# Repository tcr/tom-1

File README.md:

# TOM-1

https://hackaday.io/project/171965-ttl-operation-module-tom-1

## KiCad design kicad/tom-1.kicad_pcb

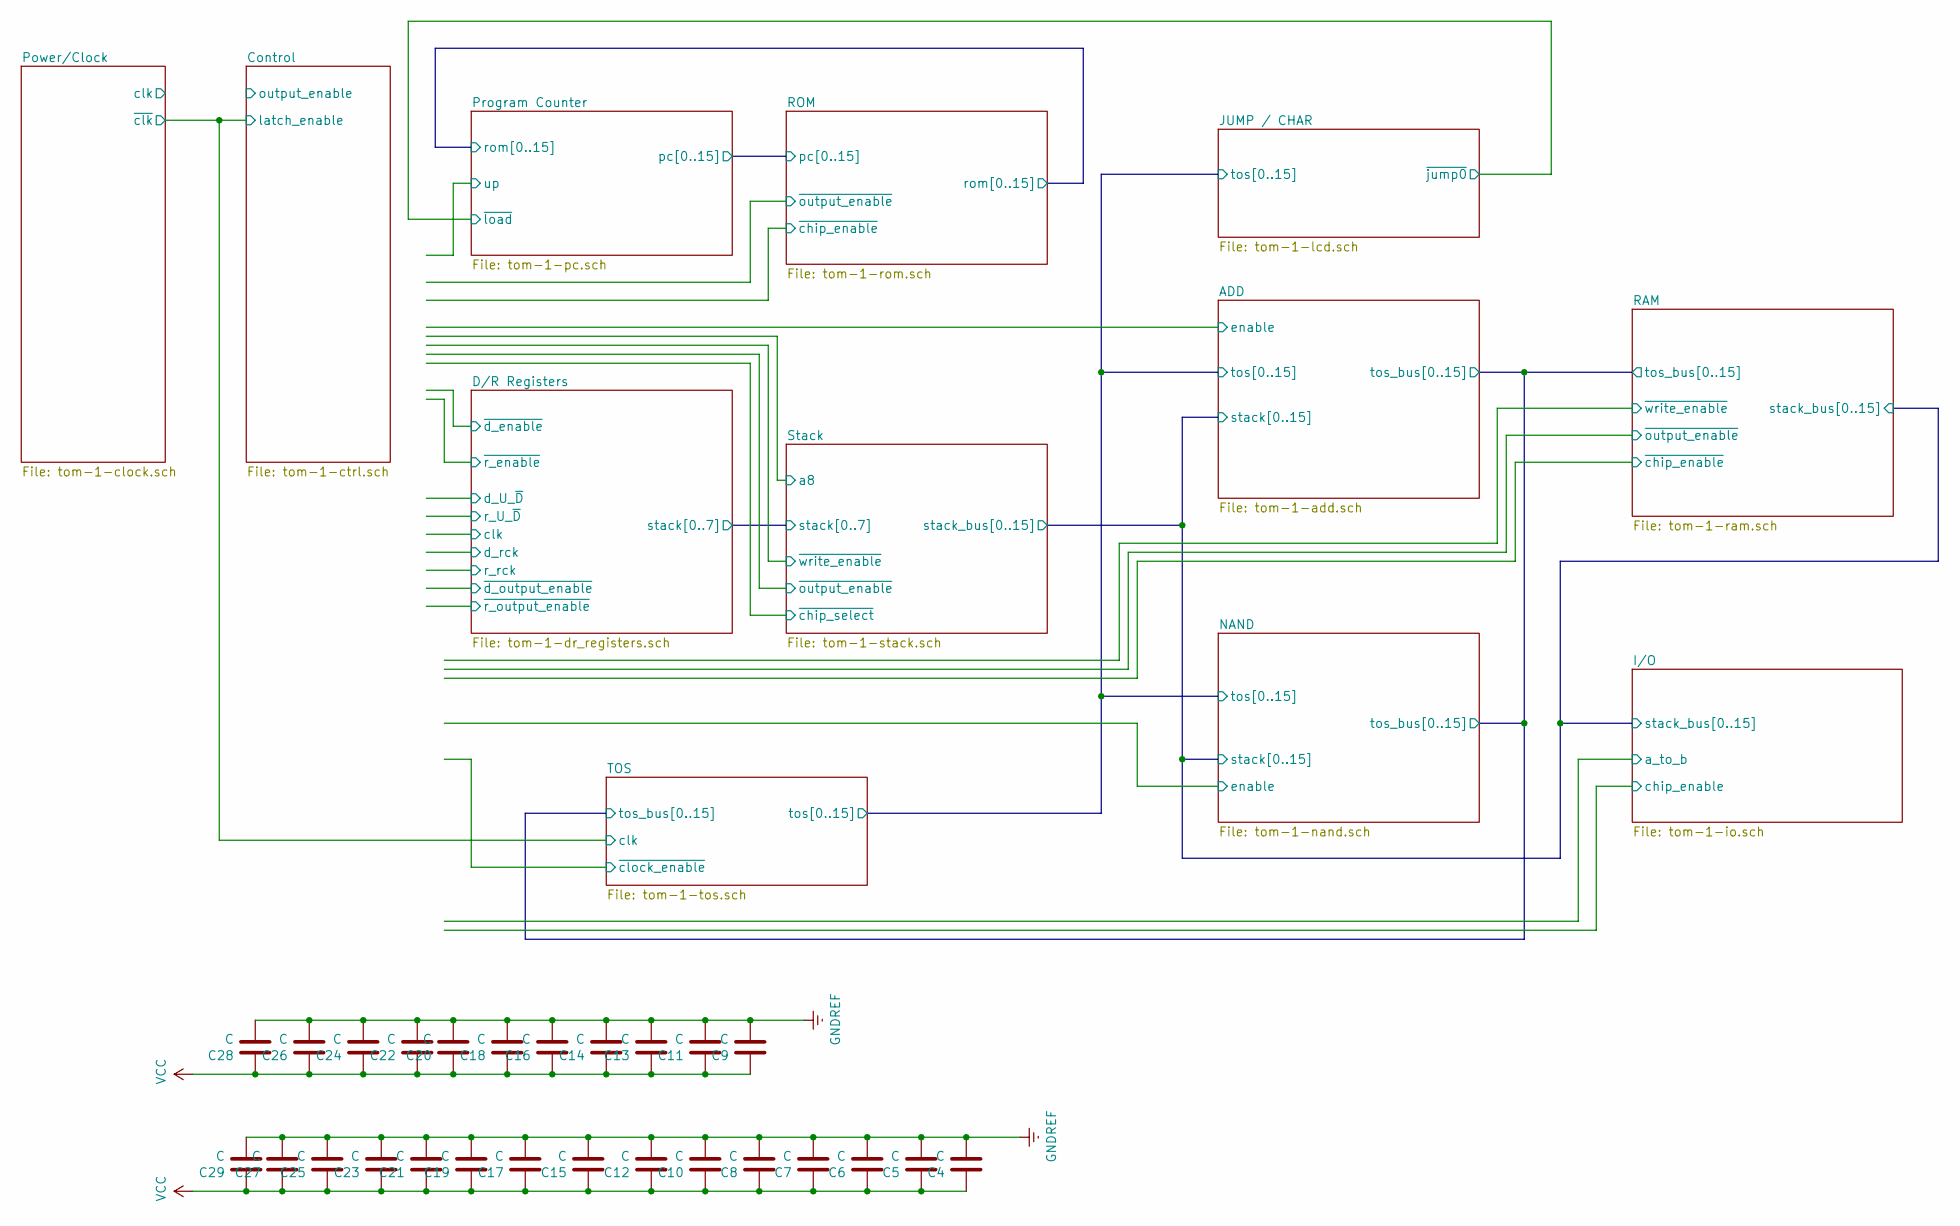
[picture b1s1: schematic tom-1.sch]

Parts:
C4, C5, C6, C7, C8, C9, C10, C11, C12, C13, C14, C15, C16, C17, C18, C19, C20, C21, C22, C23, C24, C25, C26, C27, C28, C29: C; C_Disc_D3.0mm_W1.6mm_P2.50mm

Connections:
GNDREF: C4.2, C5.1, C6.1, C7.1, C8.1, C9.2, C10.2, C11.2, C12.2, C13.2, C14.2, C15.2, C16.2, C17.2, C18.2, C19.2, C20.2, C21.2, C22.2, C23.2, C24.2, C25.2, C26.2, C27.2, C28.2, C29.2; also elsewhere on the board
VCC: C4.1, C5.2, C6.2, C7.2, C8.2, C9.1, C10.1, C11.1, C12.1, C13.1, C14.1, C15.1, C16.1, C17.1, C18.1, C19.1, C20.1, C21.1, C22.1, C23.1, C24.1, C25.1, C26.1, C27.1, C28.1, C29.1; also elsewhere on the board

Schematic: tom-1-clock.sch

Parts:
C1, C2, C3: C; C_Disc_D4.7mm_W2.5mm_P5.00mm
C30: 10uF; C_Disc_D3.0mm_W1.6mm_P2.50mm
D1: DIODE; D_DO-41_SOD81_P2.54mm_Vertical_AnodeUp
D2: LED; LED_D3.0mm
J2: USB Module; PinHeader_1x06_P2.54mm_Vertical
JP1: Jumper_NC_Dual; PinHeader_1x03_P2.54mm_Vertical
Q1: BC517; TO-92_Inline
R2, R3, R4, R7, R8, R9: R; R_Axial_DIN0204_L3.6mm_D1.6mm_P1.90mm_Vertical
R5: 1K; R_Axial_DIN0204_L3.6mm_D1.6mm_P1.90mm_Vertical
R6: 20K; R_Axial_DIN0204_L3.6mm_D1.6mm_P1.90mm_Vertical
SW1, SW2: SW_PUSH; SW_PUSH_6mm
U8: LM555xN; DIP-8_W7.62mm

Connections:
/Power/Clock/clk: R7.2, U8.3 (Q)
/TOS/clk: Q1.1 (C), R8.2; also elsewhere on the board
GND: C2.2, C3.2, SW2.1, U8.1 (GND); also elsewhere on the board
GNDREF: C30.2, J2.2, Q1.3 (E), R9.2, SW1.1; also elsewhere on the board
unnamed: C1.1, D1.1 (K), JP1.1, R3.2
unnamed: C1.2, R2.2, SW2.2
unnamed: C2.1, R4.2, U8.6 (THR), U8.7 (DIS)
unnamed: D2.1, R9.1
unnamed: JP1.2, U8.2 (TR)
unnamed: Q1.2 (B), R7.1
unnamed: R5.2, SW1.2
VCC: C3.1, D1.2 (A), D2.2, J2.1, R2.1, R3.1, R4.1, R6.1, R8.1, U8.4 (R), U8.8 (VCC); also elsewhere on the board
~Reset: C30.1, R5.1, R6.2

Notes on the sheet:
Reset generation

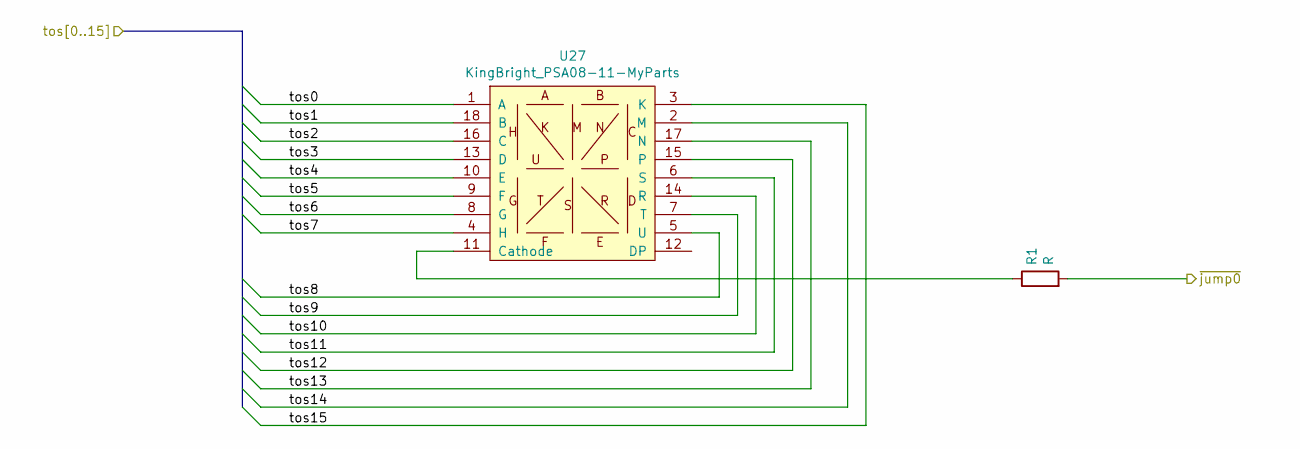
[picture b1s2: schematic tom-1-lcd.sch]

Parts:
R1: R; R_Axial_DIN0204_L3.6mm_D1.6mm_P1.90mm_Vertical
U27: KingBright_PSA08-11-MyParts; EightSegment

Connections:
/ADD/tos0: U27.1 (A); also elsewhere on the board
/ADD/tos1: U27.18 (B); also elsewhere on the board
/ADD/tos2: U27.16 (C); also elsewhere on the board
/ADD/tos3: U27.13 (D); also elsewhere on the board
/ADD/tos4: U27.10 (E); also elsewhere on the board
/ADD/tos5: U27.9 (F); also elsewhere on the board
/ADD/tos6: U27.8 (G); also elsewhere on the board
/ADD/tos7: U27.4 (H); also elsewhere on the board
/ADD/tos8: U27.5 (U); also elsewhere on the board
/ADD/tos9: U27.7 (T); also elsewhere on the board
/ADD/tos10: U27.14 (R); also elsewhere on the board
/ADD/tos11: U27.6 (S); also elsewhere on the board
/ADD/tos12: U27.15; also elsewhere on the board
/ADD/tos13: U27.17 (N); also elsewhere on the board
/ADD/tos14: U27.2 (M); also elsewhere on the board
/ADD/tos15: U27.3 (K); also elsewhere on the board
/JUMP / CHAR/jump0: R1.2; also elsewhere on the board
unnamed: R1.1, U27.11 (Cathode)

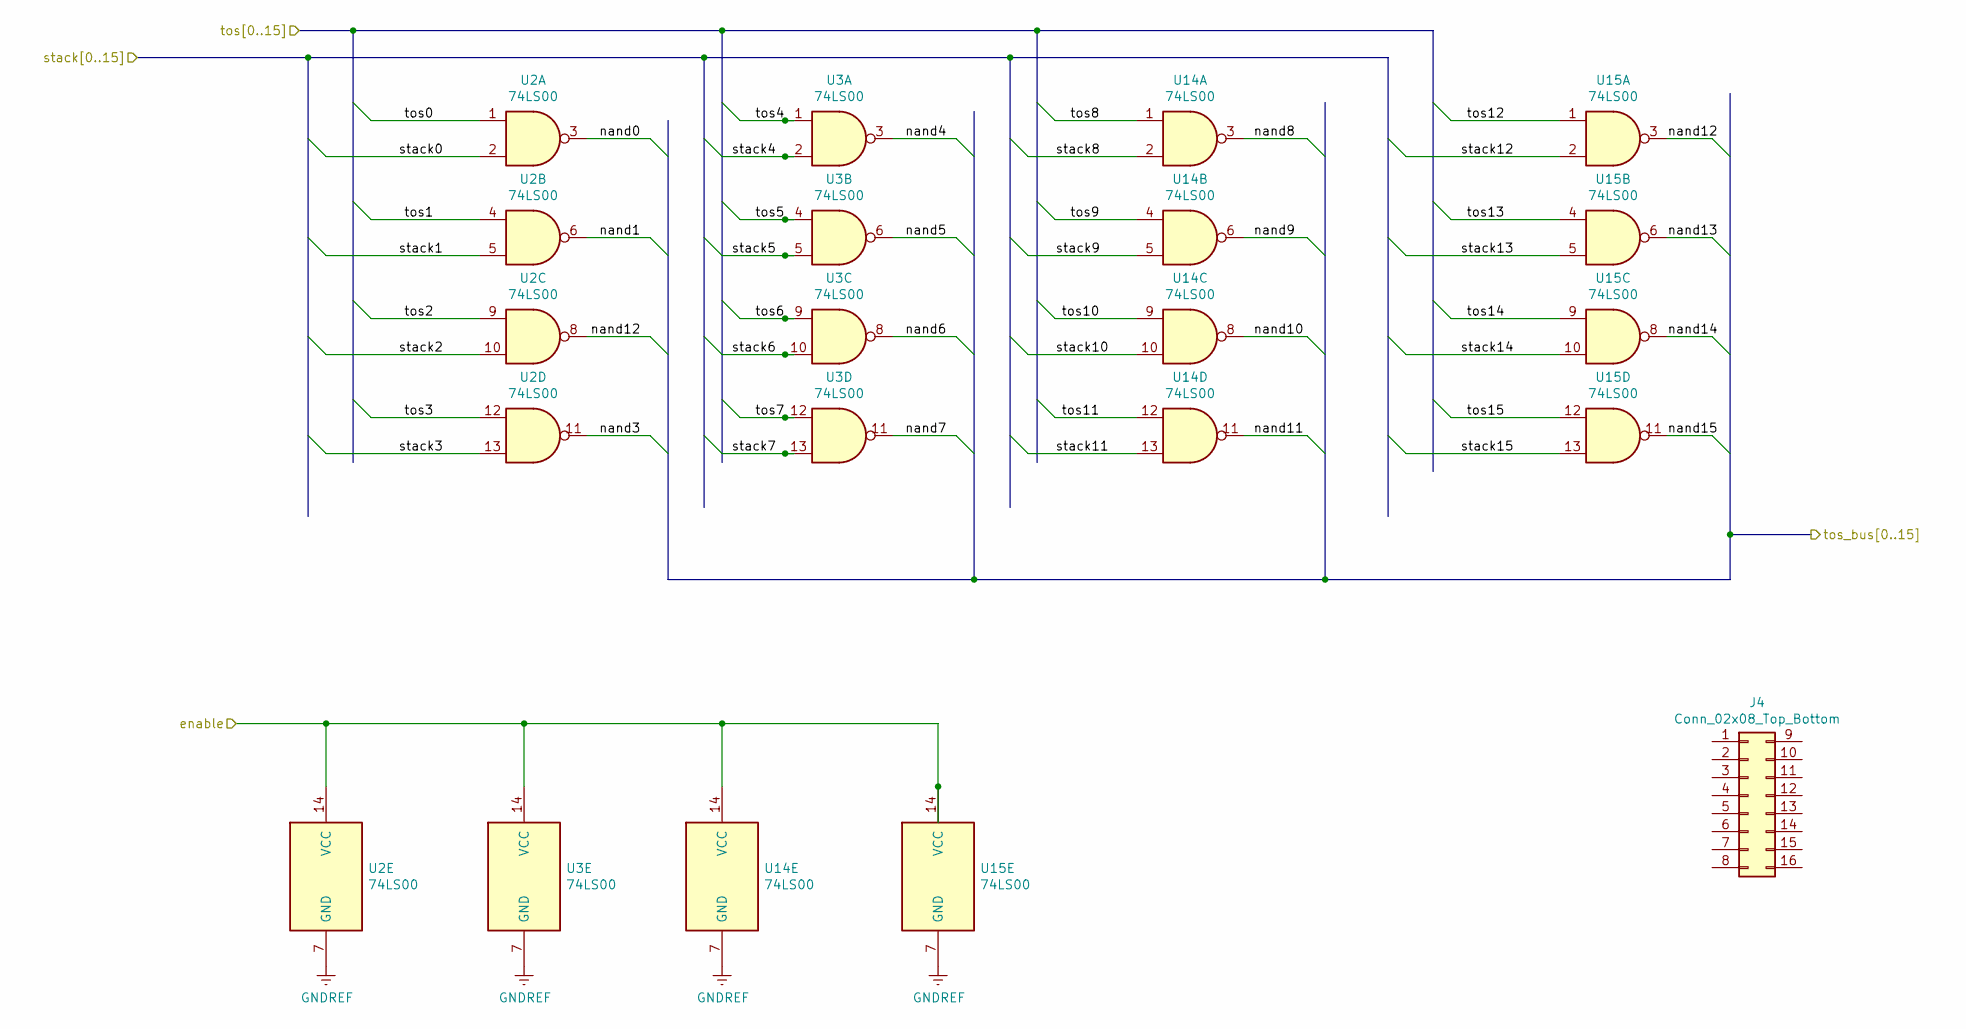
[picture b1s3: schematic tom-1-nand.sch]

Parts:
J4: Conn_02x08_Top_Bottom; PinSocket_2x09_P2.54mm_Vertical
U2, U3, U14, U15: 74LS00; DIP-14_W7.62mm

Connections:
/ADD/stack0: U2.2; also elsewhere on the board
/ADD/stack1: U2.5; also elsewhere on the board
/ADD/stack2: U2.10; also elsewhere on the board
/ADD/stack3: U2.13; also elsewhere on the board
/ADD/stack4: U3.2; also elsewhere on the board
/ADD/stack5: U3.5; also elsewhere on the board
/ADD/stack6: U3.10; also elsewhere on the board
/ADD/stack7: U3.13; also elsewhere on the board
/ADD/stack8: U14.2; also elsewhere on the board
/ADD/stack9: U14.5; also elsewhere on the board
/ADD/stack10: U14.10; also elsewhere on the board
/ADD/stack11: U14.13; also elsewhere on the board
/ADD/stack12: U15.2; also elsewhere on the board
/ADD/stack13: U15.5; also elsewhere on the board
/ADD/stack14: U15.10; also elsewhere on the board
/ADD/stack15: U15.13; also elsewhere on the board
/ADD/tos0: U2.1; also elsewhere on the board
/ADD/tos1: U2.4; also elsewhere on the board
/ADD/tos2: U2.9; also elsewhere on the board
/ADD/tos3: U2.12; also elsewhere on the board
/ADD/tos4: U3.1; also elsewhere on the board
/ADD/tos5: U3.4; also elsewhere on the board
/ADD/tos6: U3.9; also elsewhere on the board
/ADD/tos7: U3.12; also elsewhere on the board
/ADD/tos8: U14.1; also elsewhere on the board
/ADD/tos9: U14.4; also elsewhere on the board
/ADD/tos10: U14.9; also elsewhere on the board
/ADD/tos11: U14.12; also elsewhere on the board
/ADD/tos12: U15.1; also elsewhere on the board
/ADD/tos13: U15.4; also elsewhere on the board
/ADD/tos14: U15.9; also elsewhere on the board
/ADD/tos15: U15.12; also elsewhere on the board
/NAND/enable: U2.14 (VCC), U3.14 (VCC), U14.14 (VCC), U15.14 (VCC)
/NAND/nand0: U2.3
/NAND/nand1: U2.6
/NAND/nand3: U2.11
/NAND/nand4: U3.3
/NAND/nand5: U3.6
/NAND/nand6: U3.8
/NAND/nand7: U3.11
/NAND/nand8: U14.3
/NAND/nand9: U14.6
/NAND/nand10: U14.8
/NAND/nand11: U14.11
/NAND/nand12: U2.8, U15.3
/NAND/nand13: U15.6
/NAND/nand14: U15.8
/NAND/nand15: U15.11
GNDREF: U2.7 (GND), U3.7 (GND), U14.7 (GND), U15.7 (GND); also elsewhere on the board

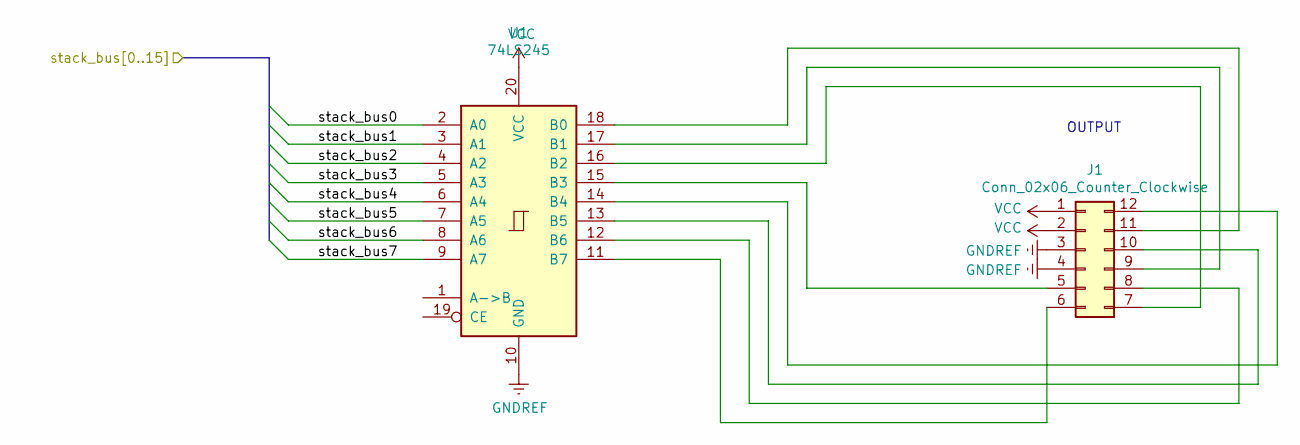
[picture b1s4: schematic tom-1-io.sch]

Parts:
J1: Conn_02x06_Counter_Clockwise; PinSocket_2x06_P2.54mm_Vertical
U1: 74LS245; DIP-20_W7.62mm

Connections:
/ADD/stack0: U1.2 (A0); also elsewhere on the board
/ADD/stack1: U1.3 (A1); also elsewhere on the board
/ADD/stack2: U1.4 (A2); also elsewhere on the board
/ADD/stack3: U1.5 (A3); also elsewhere on the board
/ADD/stack4: U1.6 (A4); also elsewhere on the board
/ADD/stack5: U1.7 (A5); also elsewhere on the board
/ADD/stack6: U1.8 (A6); also elsewhere on the board
/ADD/stack7: U1.9 (A7); also elsewhere on the board
GNDREF: J1.3, J1.4, U1.10 (GND); also elsewhere on the board
unnamed: J1.5, U1.15 (B3)
unnamed: J1.6, U1.11 (B7)
unnamed: J1.7, U1.16 (B2)
unnamed: J1.8, U1.12 (B6)
unnamed: J1.9, U1.17 (B1)
unnamed: J1.10, U1.13 (B5)
unnamed: J1.11, U1.18 (B0)
unnamed: J1.12, U1.14 (B4)
VCC: J1.1, J1.2, U1.20 (VCC); also elsewhere on the board

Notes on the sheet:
OUTPUT

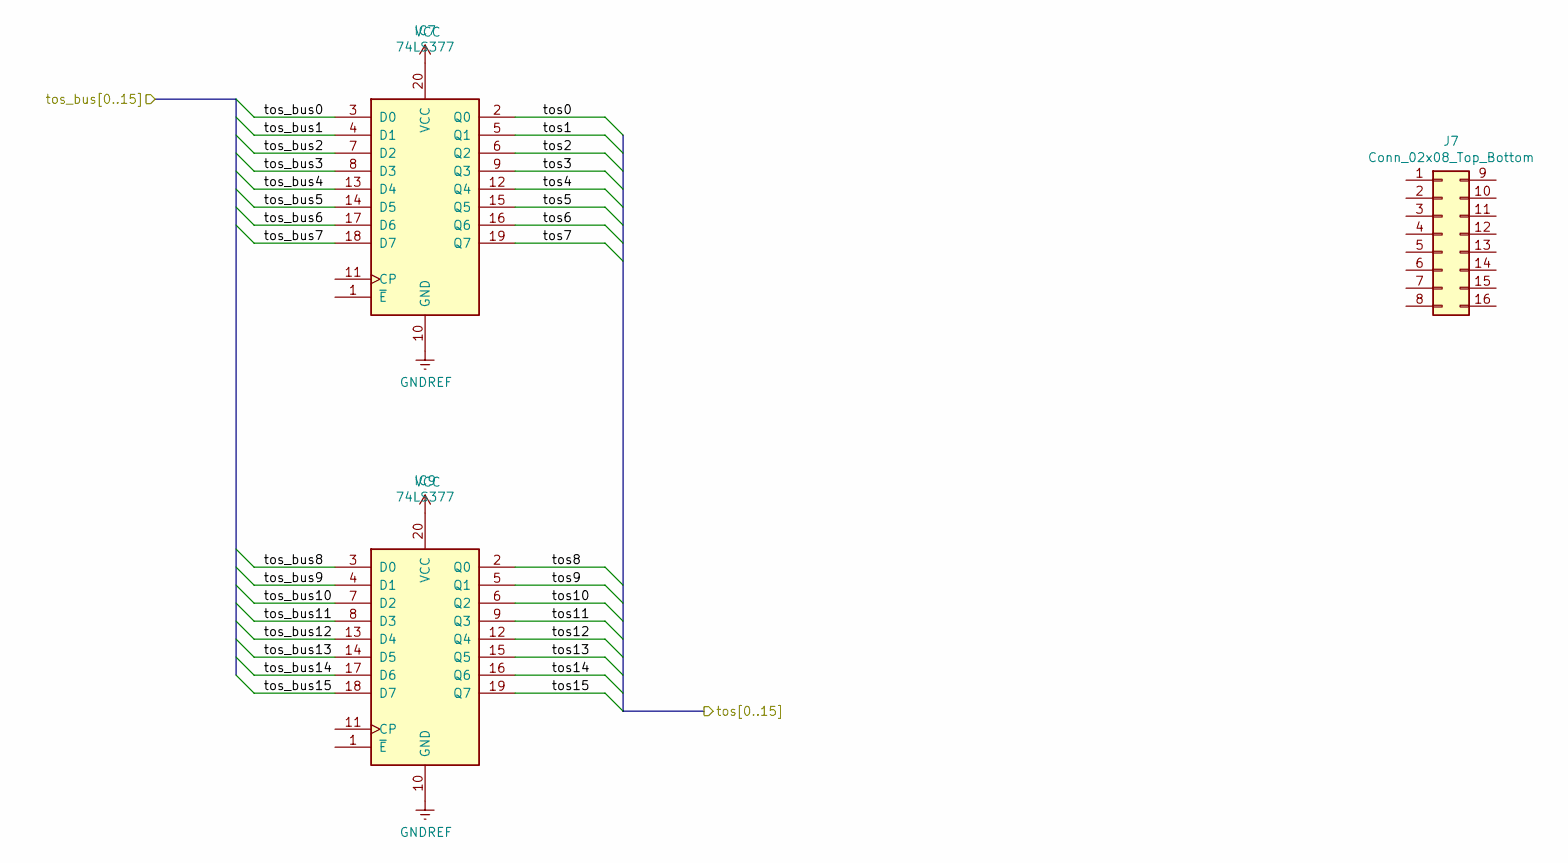
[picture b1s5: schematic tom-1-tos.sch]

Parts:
IC7, IC9: 74LS377; DIP-20_W7.62mm
J7: Conn_02x08_Top_Bottom; PinSocket_2x09_P2.54mm_Vertical

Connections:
/ADD/tos0: IC7.2 (Q0); also elsewhere on the board
/ADD/tos1: IC7.5 (Q1); also elsewhere on the board
/ADD/tos2: IC7.6 (Q2); also elsewhere on the board
/ADD/tos3: IC7.9 (Q3); also elsewhere on the board
/ADD/tos4: IC7.12 (Q4); also elsewhere on the board
/ADD/tos5: IC7.15 (Q5); also elsewhere on the board
/ADD/tos6: IC7.16 (Q6); also elsewhere on the board
/ADD/tos7: IC7.19 (Q7); also elsewhere on the board
/ADD/tos8: IC9.2 (Q0); also elsewhere on the board
/ADD/tos9: IC9.5 (Q1); also elsewhere on the board
/ADD/tos10: IC9.6 (Q2); also elsewhere on the board
/ADD/tos11: IC9.9 (Q3); also elsewhere on the board
/ADD/tos12: IC9.12 (Q4); also elsewhere on the board
/ADD/tos13: IC9.15 (Q5); also elsewhere on the board
/ADD/tos14: IC9.16 (Q6); also elsewhere on the board
/ADD/tos15: IC9.19 (Q7); also elsewhere on the board
/ADD/tos_bus0: IC7.3 (D0); also elsewhere on the board
/ADD/tos_bus1: IC7.4 (D1); also elsewhere on the board
/ADD/tos_bus2: IC7.7 (D2); also elsewhere on the board
/ADD/tos_bus3: IC7.8 (D3); also elsewhere on the board
/ADD/tos_bus4: IC7.13 (D4); also elsewhere on the board
/ADD/tos_bus5: IC7.14 (D5); also elsewhere on the board
/ADD/tos_bus6: IC7.17 (D6); also elsewhere on the board
/ADD/tos_bus7: IC7.18 (D7); also elsewhere on the board
/ADD/tos_bus8: IC9.3 (D0); also elsewhere on the board
/ADD/tos_bus9: IC9.4 (D1); also elsewhere on the board
/ADD/tos_bus10: IC9.7 (D2); also elsewhere on the board
/ADD/tos_bus11: IC9.8 (D3); also elsewhere on the board
/ADD/tos_bus12: IC9.13 (D4); also elsewhere on the board
/ADD/tos_bus13: IC9.14 (D5); also elsewhere on the board
/ADD/tos_bus14: IC9.17 (D6); also elsewhere on the board
/ADD/tos_bus15: IC9.18 (D7); also elsewhere on the board
/TOS/clk: IC7.11 (CP), IC9.11 (CP); also elsewhere on the board
/TOS/~clock_enable: IC7.1 (~E), IC9.1 (~E)
GNDREF: IC7.10 (GND), IC9.10 (GND); also elsewhere on the board
VCC: IC7.20 (VCC), IC9.20 (VCC); also elsewhere on the board

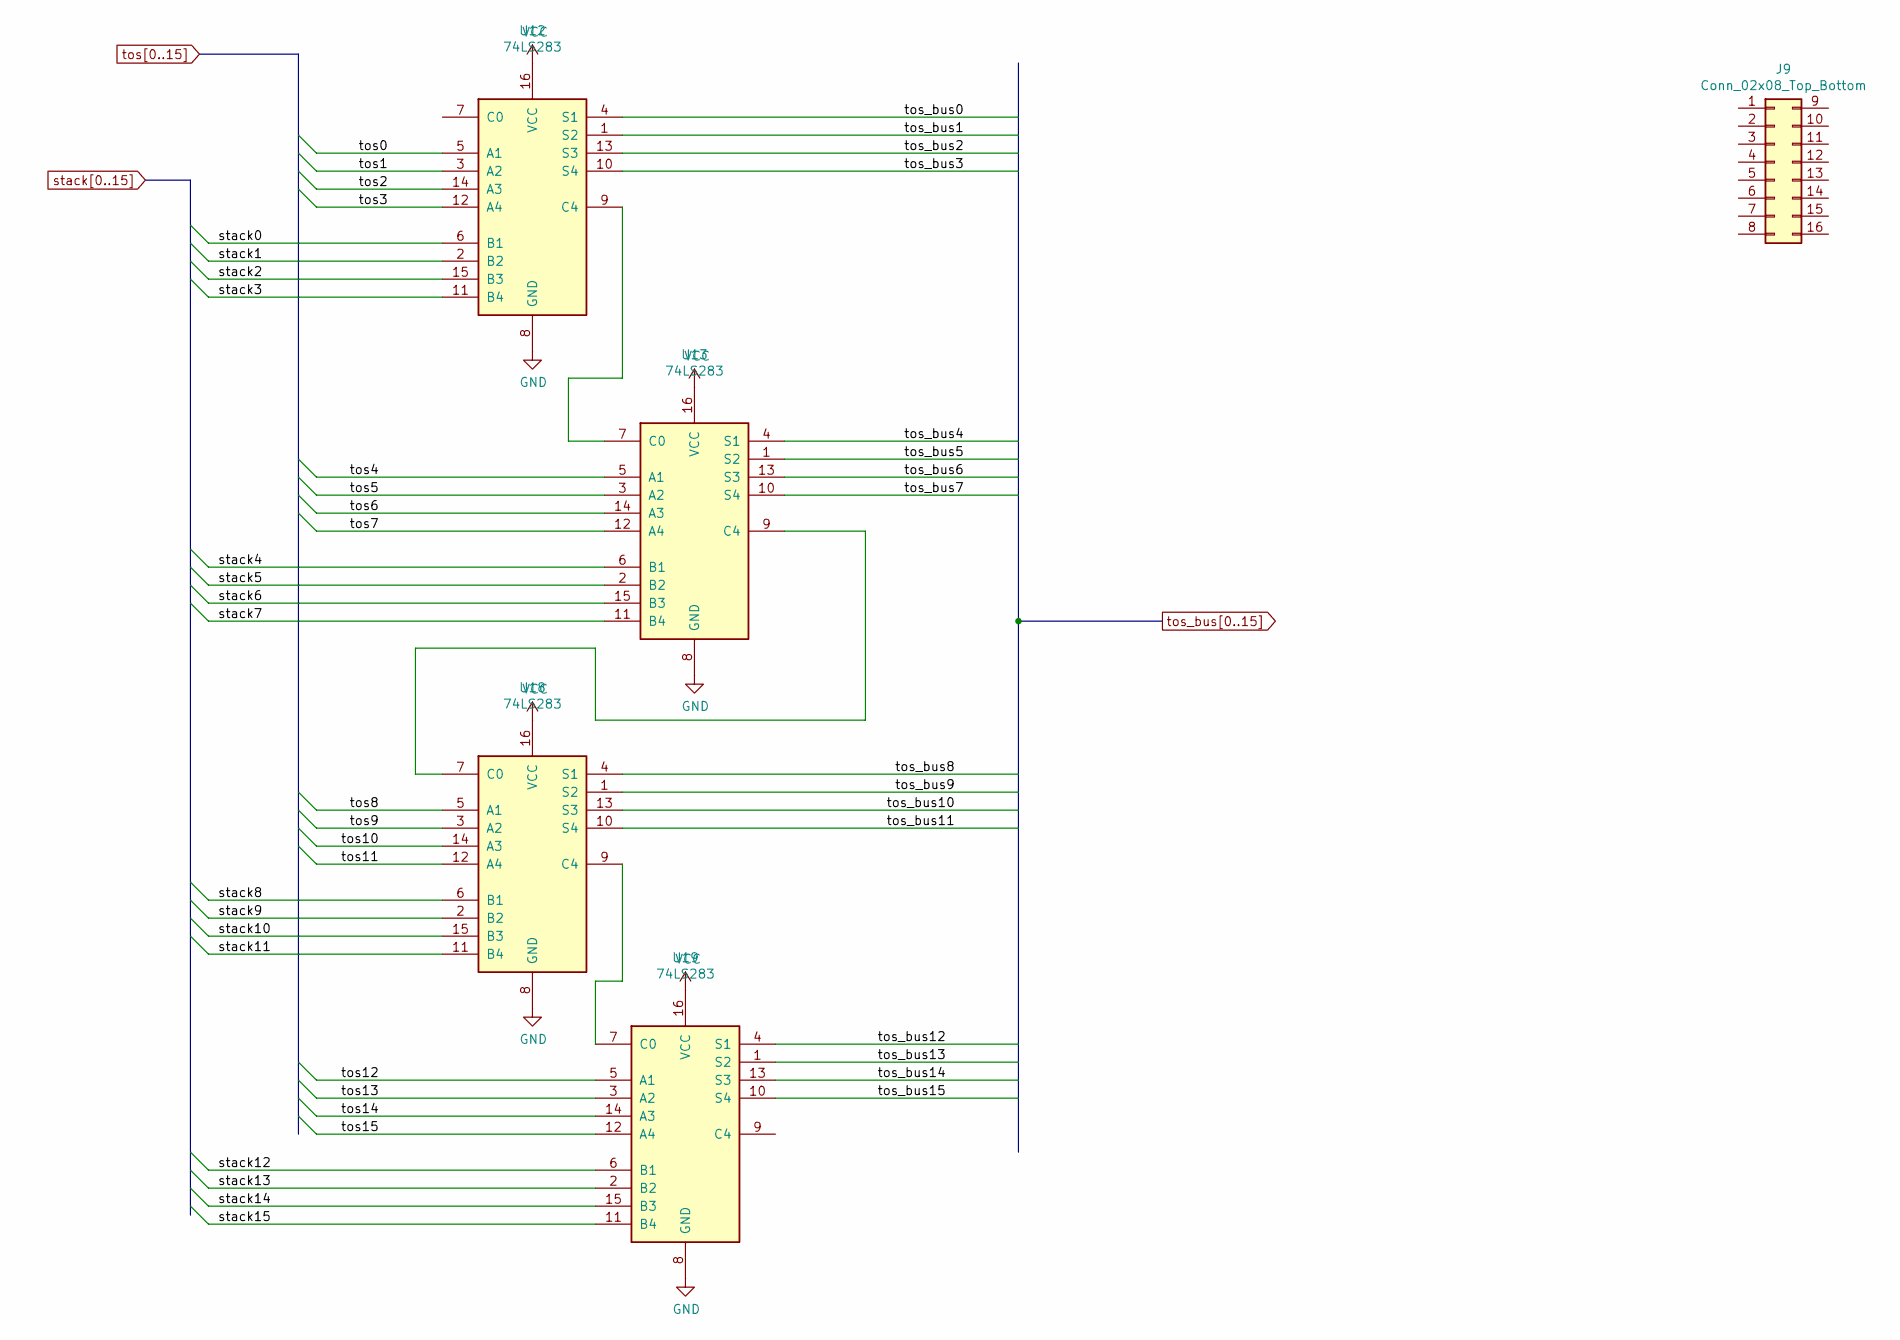
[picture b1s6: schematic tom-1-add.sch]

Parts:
J9: Conn_02x08_Top_Bottom; PinSocket_2x09_P2.54mm_Vertical
U12, U13, U18, U19: 74LS283; DIP-16_W7.62mm

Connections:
/ADD/enable: U12.16 (VCC), U13.16 (VCC), U18.16 (VCC), U19.16 (VCC)
/ADD/stack0: U12.6 (B1); also elsewhere on the board
/ADD/stack1: U12.2 (B2); also elsewhere on the board
/ADD/stack2: U12.15 (B3); also elsewhere on the board
/ADD/stack3: U12.11 (B4); also elsewhere on the board
/ADD/stack4: U13.6 (B1); also elsewhere on the board
/ADD/stack5: U13.2 (B2); also elsewhere on the board
/ADD/stack6: U13.15 (B3); also elsewhere on the board
/ADD/stack7: U13.11 (B4); also elsewhere on the board
/ADD/stack8: U18.6 (B1); also elsewhere on the board
/ADD/stack9: U18.2 (B2); also elsewhere on the board
/ADD/stack10: U18.15 (B3); also elsewhere on the board
/ADD/stack11: U18.11 (B4); also elsewhere on the board
/ADD/stack12: U19.6 (B1); also elsewhere on the board
/ADD/stack13: U19.2 (B2); also elsewhere on the board
/ADD/stack14: U19.15 (B3); also elsewhere on the board
/ADD/stack15: U19.11 (B4); also elsewhere on the board
/ADD/tos0: U12.5 (A1); also elsewhere on the board
/ADD/tos1: U12.3 (A2); also elsewhere on the board
/ADD/tos2: U12.14 (A3); also elsewhere on the board
/ADD/tos3: U12.12 (A4); also elsewhere on the board
/ADD/tos4: U13.5 (A1); also elsewhere on the board
/ADD/tos5: U13.3 (A2); also elsewhere on the board
/ADD/tos6: U13.14 (A3); also elsewhere on the board
/ADD/tos7: U13.12 (A4); also elsewhere on the board
/ADD/tos8: U18.5 (A1); also elsewhere on the board
/ADD/tos9: U18.3 (A2); also elsewhere on the board
/ADD/tos10: U18.14 (A3); also elsewhere on the board
/ADD/tos11: U18.12 (A4); also elsewhere on the board
/ADD/tos12: U19.5 (A1); also elsewhere on the board
/ADD/tos13: U19.3 (A2); also elsewhere on the board
/ADD/tos14: U19.14 (A3); also elsewhere on the board
/ADD/tos15: U19.12 (A4); also elsewhere on the board
/ADD/tos_bus0: U12.4 (S1); also elsewhere on the board
/ADD/tos_bus1: U12.1 (S2); also elsewhere on the board
/ADD/tos_bus2: U12.13 (S3); also elsewhere on the board
/ADD/tos_bus3: U12.10 (S4); also elsewhere on the board
/ADD/tos_bus4: U13.4 (S1); also elsewhere on the board
/ADD/tos_bus5: U13.1 (S2); also elsewhere on the board
/ADD/tos_bus6: U13.13 (S3); also elsewhere on the board
/ADD/tos_bus7: U13.10 (S4); also elsewhere on the board
/ADD/tos_bus8: U18.4 (S1); also elsewhere on the board
/ADD/tos_bus9: U18.1 (S2); also elsewhere on the board
/ADD/tos_bus10: U18.13 (S3); also elsewhere on the board
/ADD/tos_bus11: U18.10 (S4); also elsewhere on the board
/ADD/tos_bus12: U19.4 (S1); also elsewhere on the board
/ADD/tos_bus13: U19.1 (S2); also elsewhere on the board
/ADD/tos_bus14: U19.13 (S3); also elsewhere on the board
/ADD/tos_bus15: U19.10 (S4); also elsewhere on the board
GND: U12.8 (GND), U13.8 (GND), U18.8 (GND), U19.8 (GND); also elsewhere on the board
GNDREF: U12.7 (C0); also elsewhere on the board
unnamed: U12.9 (C4), U13.7 (C0)
unnamed: U13.9 (C4), U18.7 (C0)
unnamed: U18.9 (C4), U19.7 (C0)

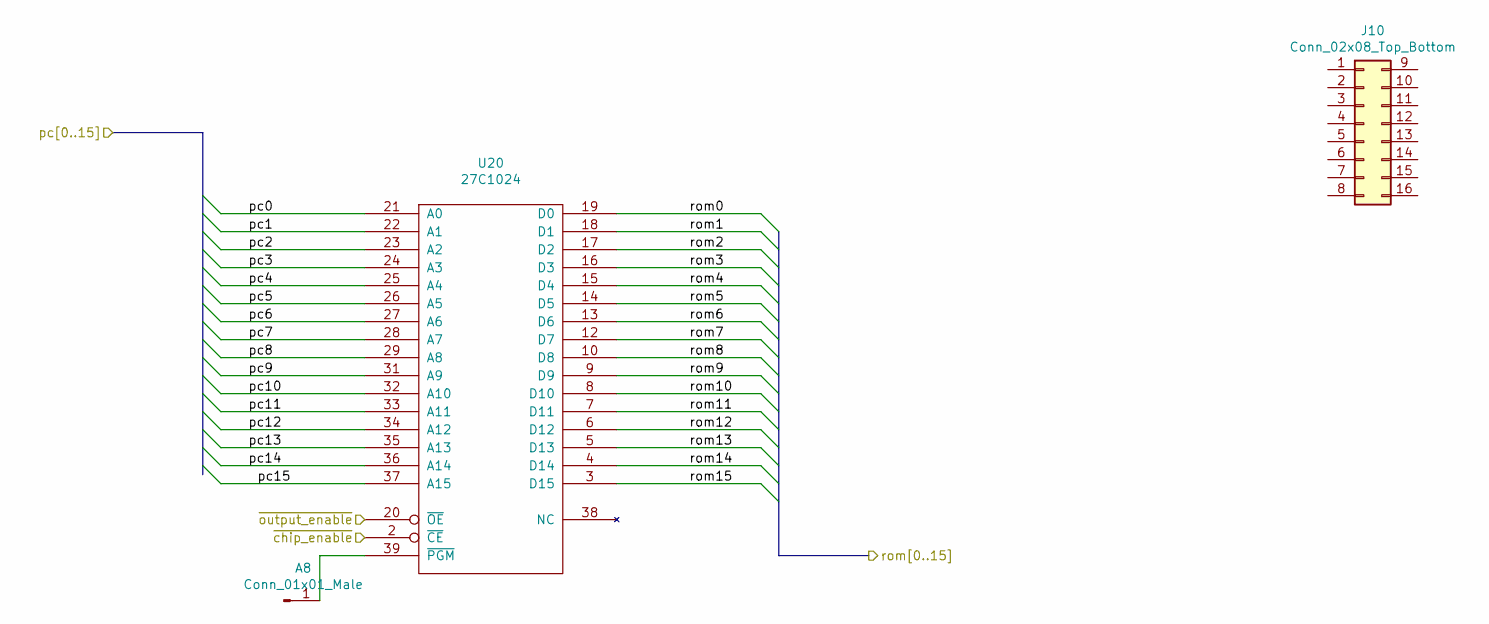
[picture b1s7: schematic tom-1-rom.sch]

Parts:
A8: Conn_01x01_Male; PinHeader_1x01_P2.54mm_Vertical
J10: Conn_02x08_Top_Bottom; PinSocket_2x09_P2.54mm_Vertical
U20: 27C1024; DIP-40_W15.24mm_Socket

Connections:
/Program Counter/pc0: U20.21 (A0); also elsewhere on the board
/Program Counter/pc1: U20.22 (A1); also elsewhere on the board
/Program Counter/pc2: U20.23 (A2); also elsewhere on the board
/Program Counter/pc3: U20.24 (A3); also elsewhere on the board
/Program Counter/pc4: U20.25 (A4); also elsewhere on the board
/Program Counter/pc5: U20.26 (A5); also elsewhere on the board
/Program Counter/pc6: U20.27 (A6); also elsewhere on the board
/Program Counter/pc7: U20.28 (A7); also elsewhere on the board
/Program Counter/pc8: U20.29 (A8); also elsewhere on the board
/Program Counter/pc9: U20.31 (A9); also elsewhere on the board
/Program Counter/pc10: U20.32 (A10); also elsewhere on the board
/Program Counter/pc11: U20.33 (A11); also elsewhere on the board
/Program Counter/pc12: U20.34 (A12); also elsewhere on the board
/Program Counter/pc13: U20.35 (A13); also elsewhere on the board
/Program Counter/pc14: U20.36 (A14); also elsewhere on the board
/Program Counter/pc15: U20.37 (A15); also elsewhere on the board
/Program Counter/rom0: U20.19 (D0); also elsewhere on the board
/Program Counter/rom1: U20.18 (D1); also elsewhere on the board
/Program Counter/rom2: U20.17 (D2); also elsewhere on the board
/Program Counter/rom3: U20.16 (D3); also elsewhere on the board
/Program Counter/rom4: U20.15 (D4); also elsewhere on the board
/Program Counter/rom5: U20.14 (D5); also elsewhere on the board
/Program Counter/rom6: U20.13 (D6); also elsewhere on the board
/Program Counter/rom7: U20.12 (D7); also elsewhere on the board
/Program Counter/rom8: U20.10 (D8); also elsewhere on the board
/Program Counter/rom9: U20.9 (D9); also elsewhere on the board
/Program Counter/rom10: U20.8 (D10); also elsewhere on the board
/Program Counter/rom11: U20.7 (D11); also elsewhere on the board
/Program Counter/rom12: U20.6 (D12); also elsewhere on the board
/Program Counter/rom13: U20.5 (D13); also elsewhere on the board
/Program Counter/rom14: U20.4 (D14); also elsewhere on the board
/Program Counter/rom15: U20.3 (D15); also elsewhere on the board
/ROM/~chip_enable~: U20.2 (~CE)
/ROM/~output_enable~: U20.20 (~OE)
GND: U20.11 (GND), U20.30 (GND); also elsewhere on the board
unnamed 282: A8.1, U20.39 (~PGM); also elsewhere on the board
VCC: U20.40 (VCC); also elsewhere on the board
VPP: U20.1 (VPP)

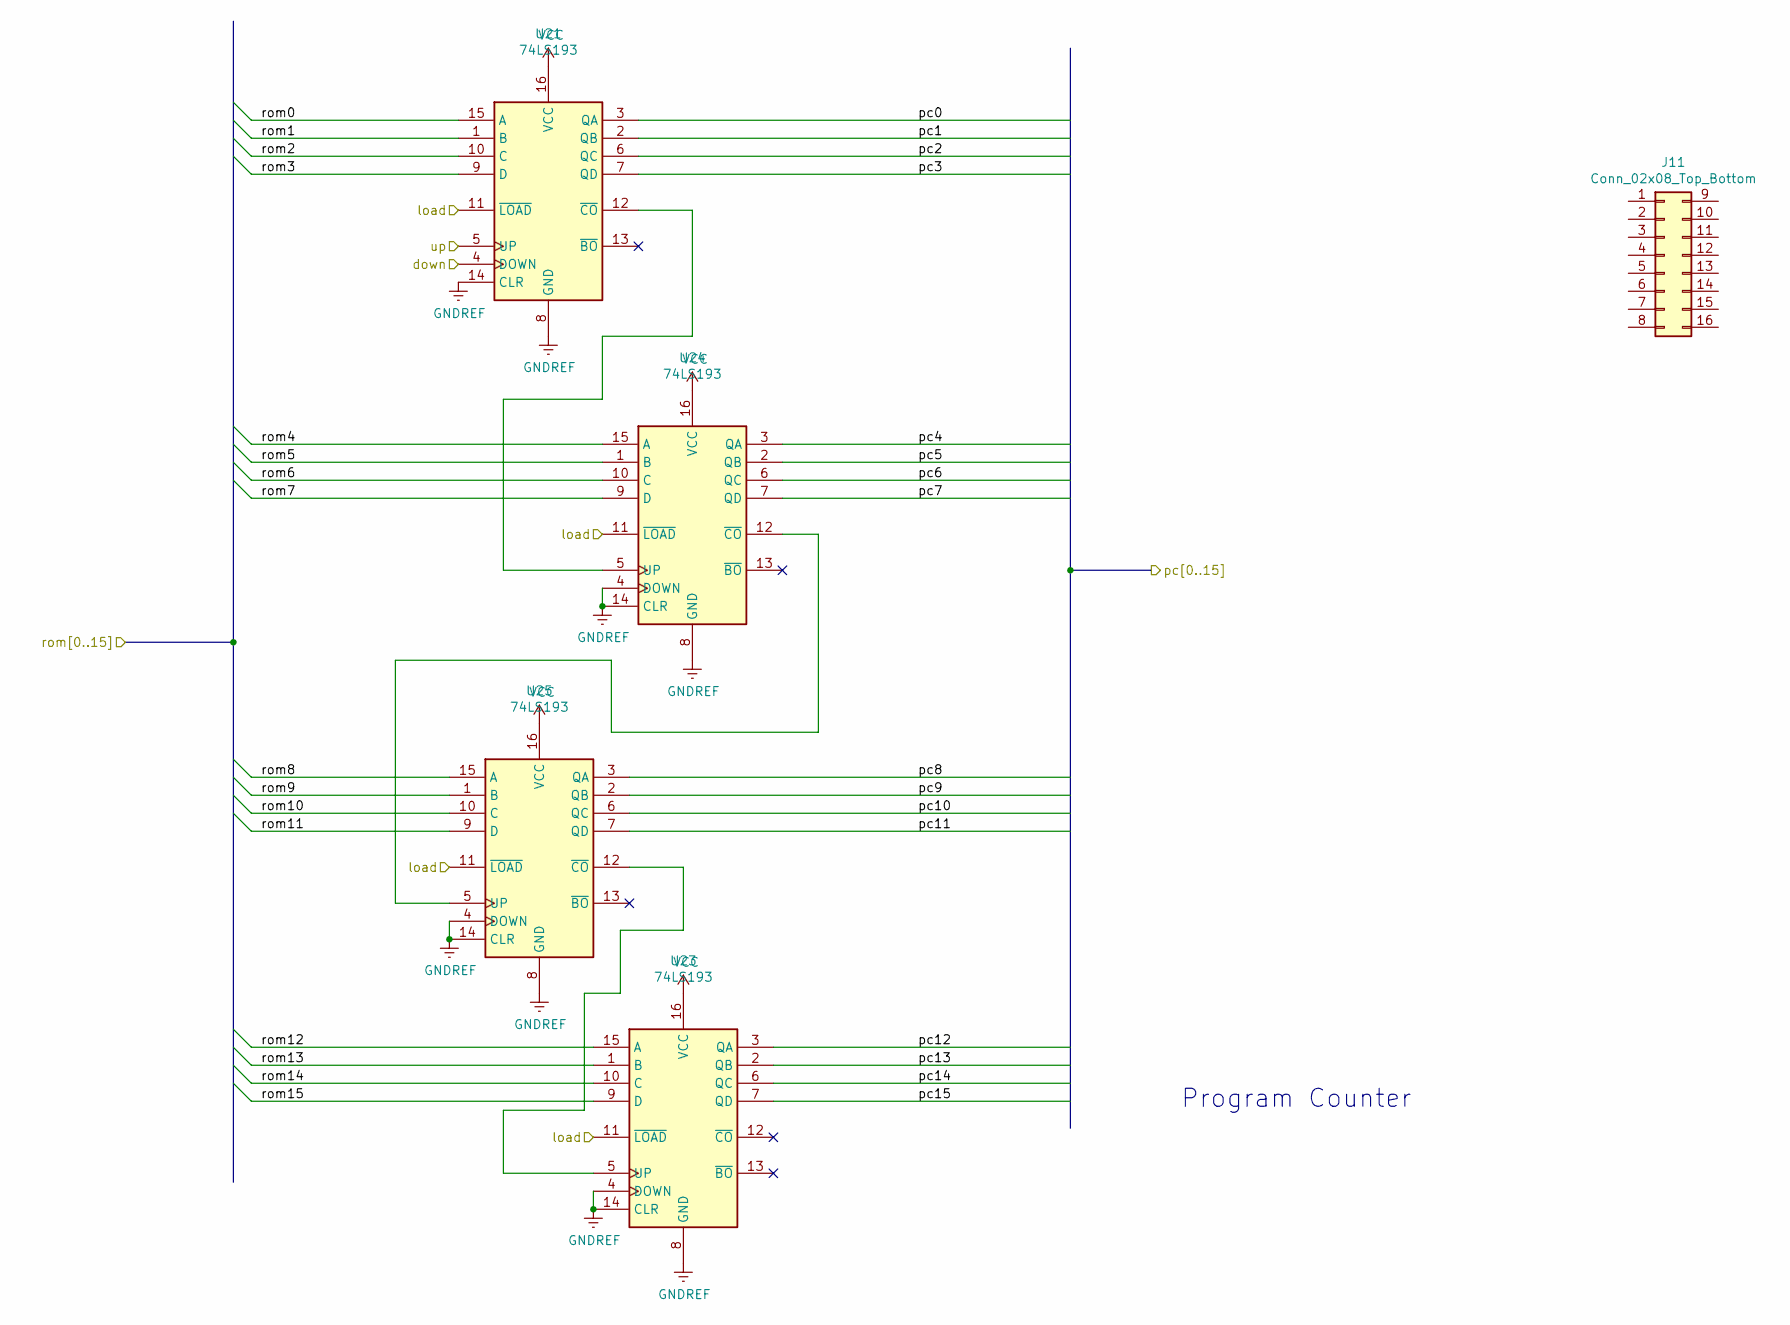
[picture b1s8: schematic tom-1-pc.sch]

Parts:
J11: Conn_02x08_Top_Bottom; PinSocket_2x09_P2.54mm_Vertical
U21, U23, U24, U25: 74LS193; DIP-16_W7.62mm

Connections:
/JUMP / CHAR/jump0: U21.11 (~LOAD), U23.11 (~LOAD), U24.11 (~LOAD), U25.11 (~LOAD); also elsewhere on the board
/Program Counter/pc0: U21.3 (QA); also elsewhere on the board
/Program Counter/pc1: U21.2 (QB); also elsewhere on the board
/Program Counter/pc2: U21.6 (QC); also elsewhere on the board
/Program Counter/pc3: U21.7 (QD); also elsewhere on the board
/Program Counter/pc4: U24.3 (QA); also elsewhere on the board
/Program Counter/pc5: U24.2 (QB); also elsewhere on the board
/Program Counter/pc6: U24.6 (QC); also elsewhere on the board
/Program Counter/pc7: U24.7 (QD); also elsewhere on the board
/Program Counter/pc8: U25.3 (QA); also elsewhere on the board
/Program Counter/pc9: U25.2 (QB); also elsewhere on the board
/Program Counter/pc10: U25.6 (QC); also elsewhere on the board
/Program Counter/pc11: U25.7 (QD); also elsewhere on the board
/Program Counter/pc12: U23.3 (QA); also elsewhere on the board
/Program Counter/pc13: U23.2 (QB); also elsewhere on the board
/Program Counter/pc14: U23.6 (QC); also elsewhere on the board
/Program Counter/pc15: U23.7 (QD); also elsewhere on the board
/Program Counter/rom0: U21.15 (A); also elsewhere on the board
/Program Counter/rom1: U21.1 (B); also elsewhere on the board
/Program Counter/rom2: U21.10 (C); also elsewhere on the board
/Program Counter/rom3: U21.9 (D); also elsewhere on the board
/Program Counter/rom4: U24.15 (A); also elsewhere on the board
/Program Counter/rom5: U24.1 (B); also elsewhere on the board
/Program Counter/rom6: U24.10 (C); also elsewhere on the board
/Program Counter/rom7: U24.9 (D); also elsewhere on the board
/Program Counter/rom8: U25.15 (A); also elsewhere on the board
/Program Counter/rom9: U25.1 (B); also elsewhere on the board
/Program Counter/rom10: U25.10 (C); also elsewhere on the board
/Program Counter/rom11: U25.9 (D); also elsewhere on the board
/Program Counter/rom12: U23.15 (A); also elsewhere on the board
/Program Counter/rom13: U23.1 (B); also elsewhere on the board
/Program Counter/rom14: U23.10 (C); also elsewhere on the board
/Program Counter/rom15: U23.9 (D); also elsewhere on the board
/Program Counter/up: U21.5 (UP)
GNDREF: U21.4 (DOWN), U21.8 (GND), U21.14 (CLR), U23.4 (DOWN), U23.8 (GND), U23.14 (CLR), U24.4 (DOWN), U24.8 (GND), U24.14 (CLR), U25.4 (DOWN), U25.8 (GND), U25.14 (CLR); also elsewhere on the board
unnamed: U21.12 (~CO), U24.5 (UP)
unnamed: U23.5 (UP), U25.12 (~CO)
unnamed: U24.12 (~CO), U25.5 (UP)
VCC: U21.16 (VCC), U23.16 (VCC), U24.16 (VCC), U25.16 (VCC); also elsewhere on the board

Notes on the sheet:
Program Counter
